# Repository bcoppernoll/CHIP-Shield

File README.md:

# CHIP-Shield
Basic board layout for a shield for the CHIP

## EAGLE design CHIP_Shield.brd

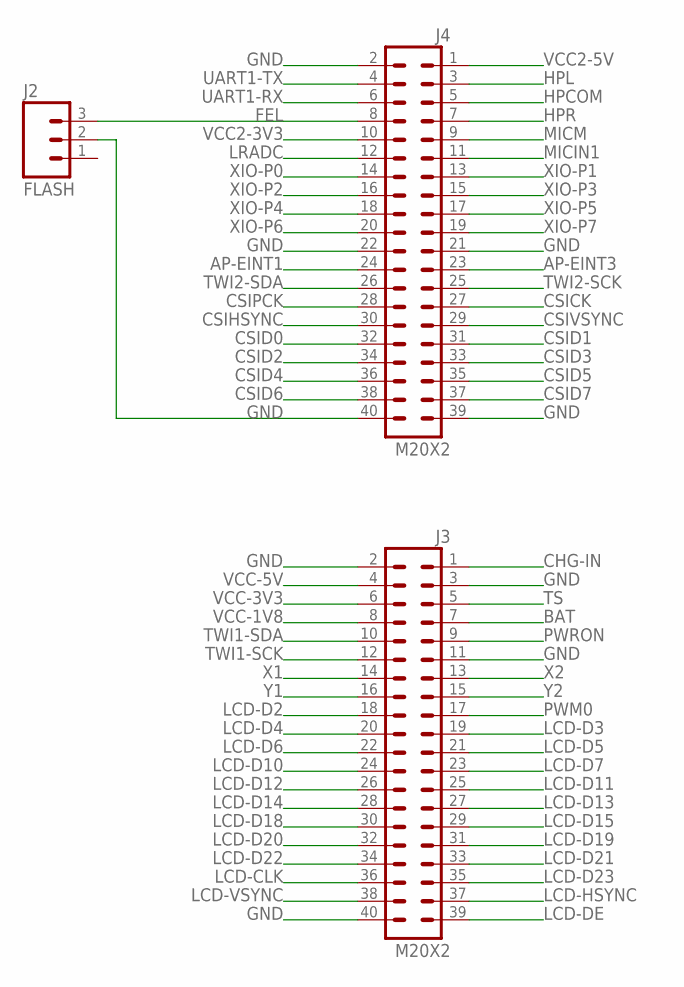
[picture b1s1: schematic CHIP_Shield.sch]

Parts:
J2: FLASH; 1X03
J3, J4: M20X2; 2X20

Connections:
AP-EINT1: J4.24
AP-EINT3: J4.23
BAT: J3.7
CHG-IN: J3.1
CSICK: J4.27
CSID0: J4.32
CSID1: J4.31
CSID2: J4.34
CSID3: J4.33
CSID4: J4.36
CSID5: J4.35
CSID6: J4.38
CSID7: J4.37
CSIHSYNC: J4.30
CSIPCK: J4.28
CSIVSYNC: J4.29
FEL: J2.3, J4.8
GND: J2.2, J3.2, J3.3, J3.11, J3.40, J4.2, J4.21, J4.22, J4.39, J4.40
HPCOM: J4.5
HPL: J4.3
HPR: J4.7
LCD-CLK: J3.36
LCD-D2: J3.18
LCD-D3: J3.19
LCD-D4: J3.20
LCD-D5: J3.21
LCD-D6: J3.22
LCD-D7: J3.23
LCD-D10: J3.24
LCD-D11: J3.25
LCD-D12: J3.26
LCD-D13: J3.27
LCD-D14: J3.28
LCD-D15: J3.29
LCD-D18: J3.30
LCD-D19: J3.31
LCD-D20: J3.32
LCD-D21: J3.33
LCD-D22: J3.34
LCD-D23: J3.35
LCD-DE: J3.39
LCD-HSYNC: J3.37
LCD-VSYNC: J3.38
LRADC: J4.12
MICIN1: J4.11
MICM: J4.9
PWM0: J3.17
PWRON: J3.9
TS: J3.5
TWI1-SCK: J3.12
TWI1-SDA: J3.10
TWI2-SCK: J4.25
TWI2-SDA: J4.26
UART1-RX: J4.6
UART1-TX: J4.4
VCC2-3V3: J4.10
VCC2-5V: J4.1
VCC-1V8: J3.8
VCC-3V3: J3.6
VCC-5V: J3.4
X1: J3.14
X2: J3.13
XIO-P0: J4.14
XIO-P1: J4.13
XIO-P2: J4.16
XIO-P3: J4.15
XIO-P4: J4.18
XIO-P5: J4.17
XIO-P6: J4.20
XIO-P7: J4.19
Y1: J3.16
Y2: J3.15

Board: 2 copper layers, 3 parts (2 on the bottom side), 2 nets, no tracks yet.

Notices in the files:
parts and their libraries:
SparkFun-Connectors: Licensing: Creative Commons ShareAlike 4.0 International - https://creativecommons.org/licenses/by-sa/4.0
